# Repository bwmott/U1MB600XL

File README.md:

# Ultimate 1MB 600XL Adapter
The Ultimate 1MB 600XL Adapter is an open hardware PCB that helps with installing an Ultimate 1MB upgrade into an Atari 600XL computer. The [Ultimate 1MB](https://lotharek.pl/productdetail.php?id=56) is a popular upgrade for Atari 8-bit computers, which expands the system's memory to 1MB of RAM, offers a selectable flash memory-based ROM, and includes a Real Time Clock module. Prior to installing an Ultimate 1MB into an Atari 600XL computer, the system must be upgraded to 64KB of RAM (stock 600XLs only contain 16KB of RAM). There are several options for [upgrading a 600XL to 64KB](https://www.mathyvannisselroy.nl/xl600k64.htm).

The Ultimate 1MB 600XL Adapter allows the Ultimate 1MB to be installed in an Atari 600XL without any modifications to the case or motherboard (beyond soldering fours wires required by the Ultimate 1MB) and enables the RF shielding to be retained, if desired. Retaining the RF shielding requires relocating the coin cell battery holder from the Ultimate 1MB board to the Ultimate 1MB 600XL Adapter board.

## Components
In addition to an Ultimate 1MB and an Ultimate 1MB 600XL Adapter PCB, you'll need the following components to complete the build:

* (1) 2x5 10 Pos Receptacle (DigiKey A32955-ND; 6.73mm height) (U1MB_P2P4)
* (1) 2x10 20 Pos Receptacle (DigiKey A26490-ND; 6.73mm height) (U1MB_P5)
* (1) 2x15 30 Pos Receptacle (DigiKey A26494-ND; 6.73mm height) (U1MB_P1)
* (2) 12 Pin Header (DigiKey SAM1101-12-ND; low profile) (BASIC_U4)
* (1) 2 Pin Right Angle Header (U1MB_BAT1)
* (1) 4 Pin Right Angle Header (CPU_P2)
* (1) 5 Pin Right Angle Header (AUX_P4)
* (1) 2x10 20 Pin Right Angle Header (MMU_U2)
* (2) 0.1UF 25V Cap 0603 (DigiKey 732-7989-1-ND) (C1 & C2). (These can be skipped.)

If you would like to retain the RF shielding then the 2x5, 2x10, and 2x15 receptacles that the Ultimate 1MB upgrade plugs into should be no more than 6.73mm tall. In addition, a pair of low profile pin headers must be used on the adapter to plug into the 600XL's BASIC socket. The DigiKey part numbers listed above are versions that allow retaining the RF shielding. (To reduce the potential for damaging the BASIC socket, round pin headers such as Digikey part number SAM1000-12-ND are likely better than the square ones listed above; however, this hasn't been tested.) If you're not planning on retaining the RF shielding, then cheaper receptacles and pin headers can be utilized.

## Adapter Assembly
Here are all the parts and the PCB prior to building the Ultimate 1MB 600XL Adapter board.

Here are photos of the top and bottom of the Ultimate 1MB 600XL Adapter board after all of the components have been assembled.

Here we see the board after transplanting the coil cell battery holder from the Ultimate 1MB to the Ultimate 1MB Adapter board and running wires back to the Ultimate 1MB to provide power for its RTC. Be extra careful not to reverse the connection to the battery. We also see some insulation added on top of the BASIC pin headers to ensure that none of the pins accidentally touch the ROM socket pins on the Ultimate 1MB board when the two boards are plugged together.

## Adapter Installation
The Ultimate 1MB plugs directly on top of the Ultimate 1MB 600XL Adapter board once assembled. The adapter board can then be plugged into the 600XL's BASIC socket after removing both the BASIC and OS ROMs from the 600XL. The adapter board is designed such that the "jumper" settings on the motherboard for the type of BASIC ROM should not matter; however, the adapter board has only been tested using a stock NTSC 600XL.

You'll also need to connect the MMU cable and other motherboard signals to the adapter board like they are in a standard Ultimate 1MB installation. 

If you're retaining the RF shielding then you'll need to ensure the top of the Ultimate 1MB is insulated from the RF shield. A small piece of plastic attached to the board should work fine.

## Acknowledgements
* SukkoPera for the [DIP-24_W15.24mm-Notch KiCad foorprint](https://github.com/SukkoPera/Open2327RomAdapter/) which is used to provide a better 3D preview of the Ultimate 1MB 600XL Adapter.
* Michael St. Pierre for the Ultimate 1MB socket schematics used in the [1088 XEL Mini-ITX Motherboard](https://ataribits.weebly.com/1088xel.html) which were referenced during the design of the Ultimate 1MB 600XL Adapter.

## License
Copyright (c) 2021 by Bradford W. Mott. This source describes Open Hardware and is licensed under the CERN-OHL-W v2.

You may redistribute and modify this source and make products using it under the terms of the CERN-OHL-W v2 or later (https:/cern.ch/cern-ohl). This source is distributed WITHOUT ANY EXPRESS OR IMPLIED WARRANTY, INCLUDING OF MERCHANTABILITY, SATISFACTORY QUALITY AND FITNESS FOR A PARTICULAR PURPOSE. Please see the CERN-OHL-W v2 for applicable conditions.

Source location: https://github.com/bwmott/U1MB600XL

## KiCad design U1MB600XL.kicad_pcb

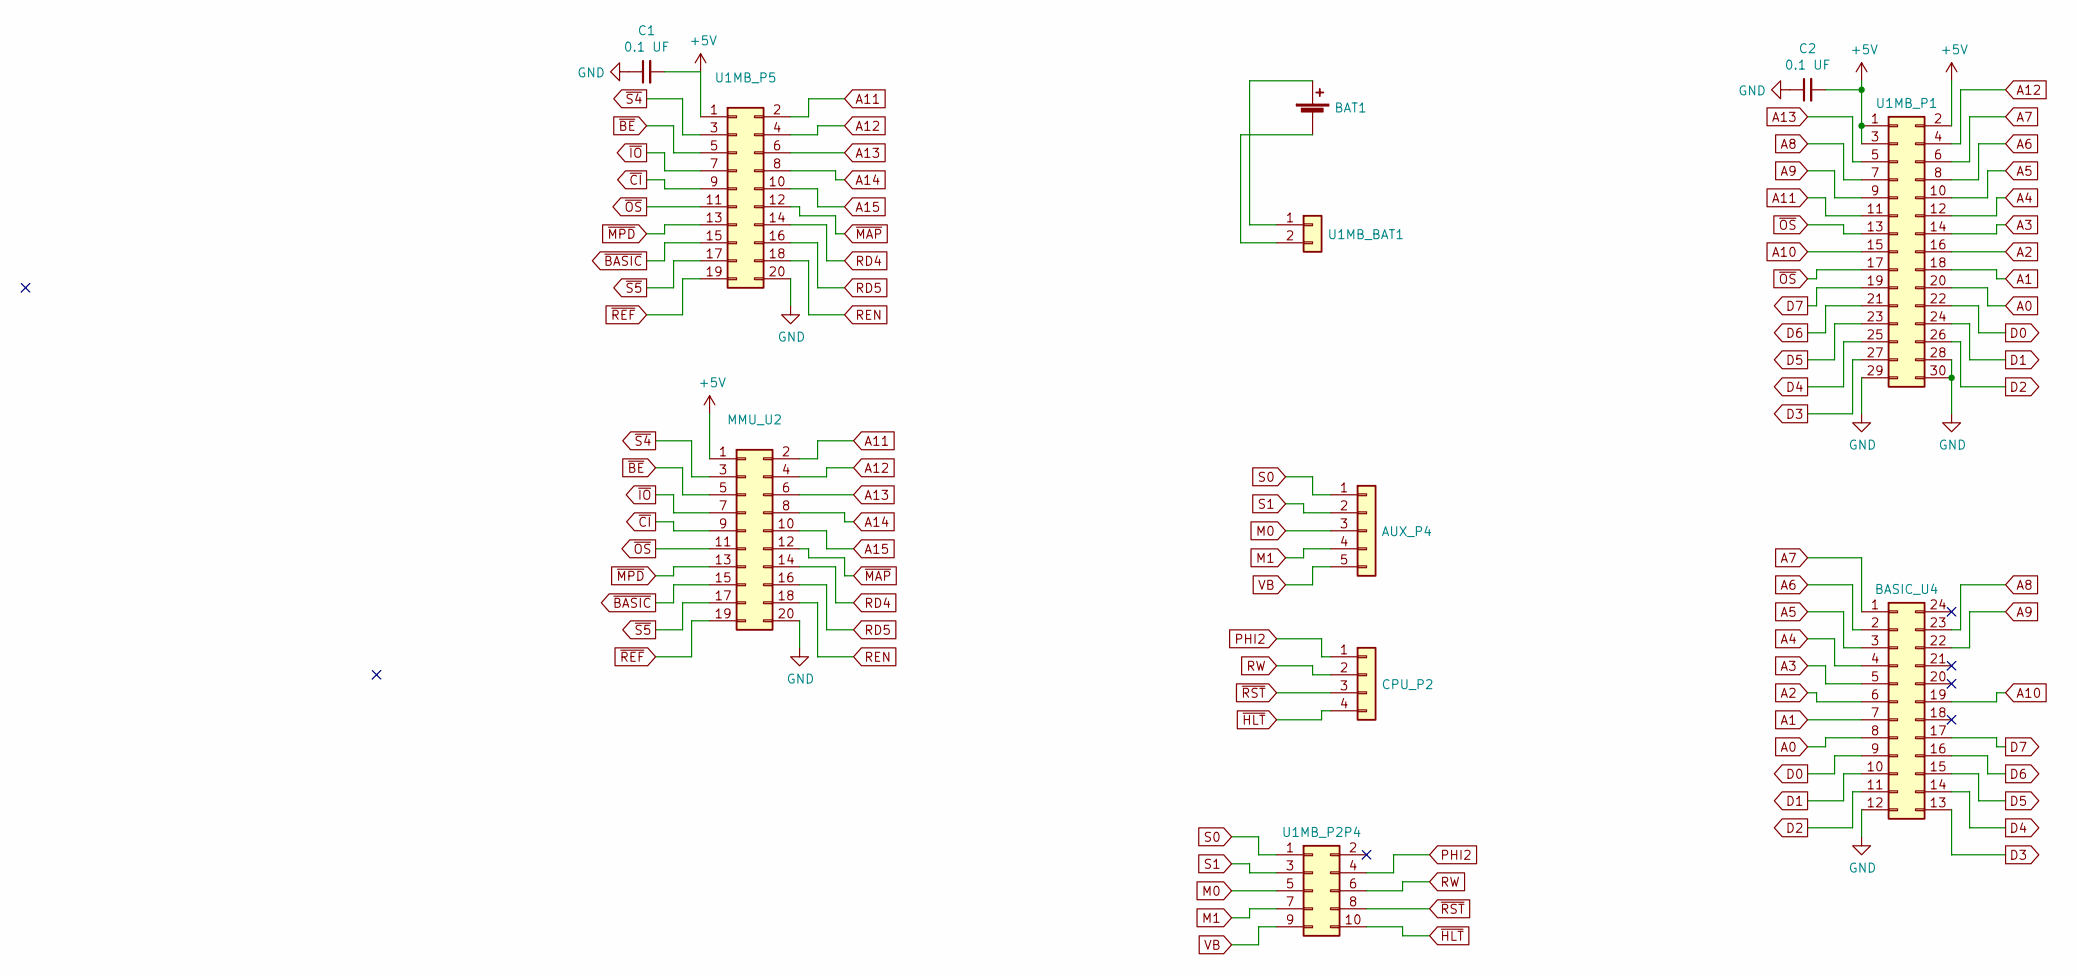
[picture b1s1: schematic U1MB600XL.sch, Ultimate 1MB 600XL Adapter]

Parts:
AUX_P4: Conn_01x05; PinHeader_1x05_P2.54mm_Horizontal
BASIC_U4: Conn_02x12_Counter_Clockwise; DIP-24_W15.24mm-Notch
BAT1: Battery_Cell; BatteryHolder_Keystone_1060_1x2032
C1, C2: 0.1 UF; C_0603_1608Metric
CPU_P2: Conn_01x04; PinHeader_1x04_P2.54mm_Horizontal
MMU_U2: Conn_02x10_Odd_Even; IDC-Header_2x10_P2.54mm_Horizontal
U1MB_BAT1: Conn_01x02; PinHeader_1x02_P2.54mm_Horizontal
U1MB_P1: Conn_02x15_Counter_Clockwise; PinSocket_2x15_P2.54mm_Vertical
U1MB_P2P4: Conn_02x05_Row_Letter_First; PinSocket_2x05_P2.54mm_Vertical
U1MB_P5: Conn_02x10_Odd_Even; PinSocket_2x10_P2.54mm_Vertical

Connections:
+5V: C1.2, C2.2, MMU_U2.1, U1MB_P1.1, U1MB_P1.2, U1MB_P1.3, U1MB_P5.1
A0: BASIC_U4.8, U1MB_P1.20
A1: BASIC_U4.7, U1MB_P1.18
A2: BASIC_U4.6, U1MB_P1.16
A3: BASIC_U4.5, U1MB_P1.14
A4: BASIC_U4.4, U1MB_P1.12
A5: BASIC_U4.3, U1MB_P1.10
A6: BASIC_U4.2, U1MB_P1.8
A7: BASIC_U4.1, U1MB_P1.6
A8: BASIC_U4.23, U1MB_P1.7
A9: BASIC_U4.22, U1MB_P1.9
A10: BASIC_U4.19, U1MB_P1.15
A11: MMU_U2.2, U1MB_P1.11, U1MB_P5.2
A12: MMU_U2.4, U1MB_P1.4, U1MB_P5.4
A13: MMU_U2.6, U1MB_P1.5, U1MB_P5.6
A14: MMU_U2.8, U1MB_P5.8
A15: MMU_U2.10, U1MB_P5.10
D0: BASIC_U4.9, U1MB_P1.22
D1: BASIC_U4.10, U1MB_P1.24
D2: BASIC_U4.11, U1MB_P1.26
D3: BASIC_U4.13, U1MB_P1.27
D4: BASIC_U4.14, U1MB_P1.25
D5: BASIC_U4.15, U1MB_P1.23
D6: BASIC_U4.16, U1MB_P1.21
D7: BASIC_U4.17, U1MB_P1.19
GND: BASIC_U4.12, C1.1, C2.1, MMU_U2.20, U1MB_P1.28, U1MB_P1.29, U1MB_P1.30, U1MB_P5.20
M0: AUX_P4.3, U1MB_P2P4.5
M1: AUX_P4.4, U1MB_P2P4.7
unnamed: BAT1.1 (+), U1MB_BAT1.1
unnamed: BAT1.2 (-), U1MB_BAT1.2
PHI2: CPU_P2.1, U1MB_P2P4.4
RD4: MMU_U2.14, U1MB_P5.14
RD5: MMU_U2.16, U1MB_P5.16
REN: MMU_U2.18, U1MB_P5.18
RW: CPU_P2.2, U1MB_P2P4.6
S0: AUX_P4.1, U1MB_P2P4.1
S1: AUX_P4.2, U1MB_P2P4.3
VB: AUX_P4.5, U1MB_P2P4.9
~BASIC: MMU_U2.15, U1MB_P5.15
~BE: MMU_U2.5, U1MB_P5.5
~CI: MMU_U2.9, U1MB_P5.9
~HLT: CPU_P2.4, U1MB_P2P4.10
~IO: MMU_U2.7, U1MB_P5.7
~MAP: MMU_U2.12, U1MB_P5.12
~MPD: MMU_U2.13, U1MB_P5.13
~OS: MMU_U2.11, U1MB_P1.13, U1MB_P1.17, U1MB_P5.11
~REF: MMU_U2.19, U1MB_P5.19
~RST: CPU_P2.3, U1MB_P2P4.8
~S4: MMU_U2.3, U1MB_P5.3
~S5: MMU_U2.17, U1MB_P5.17

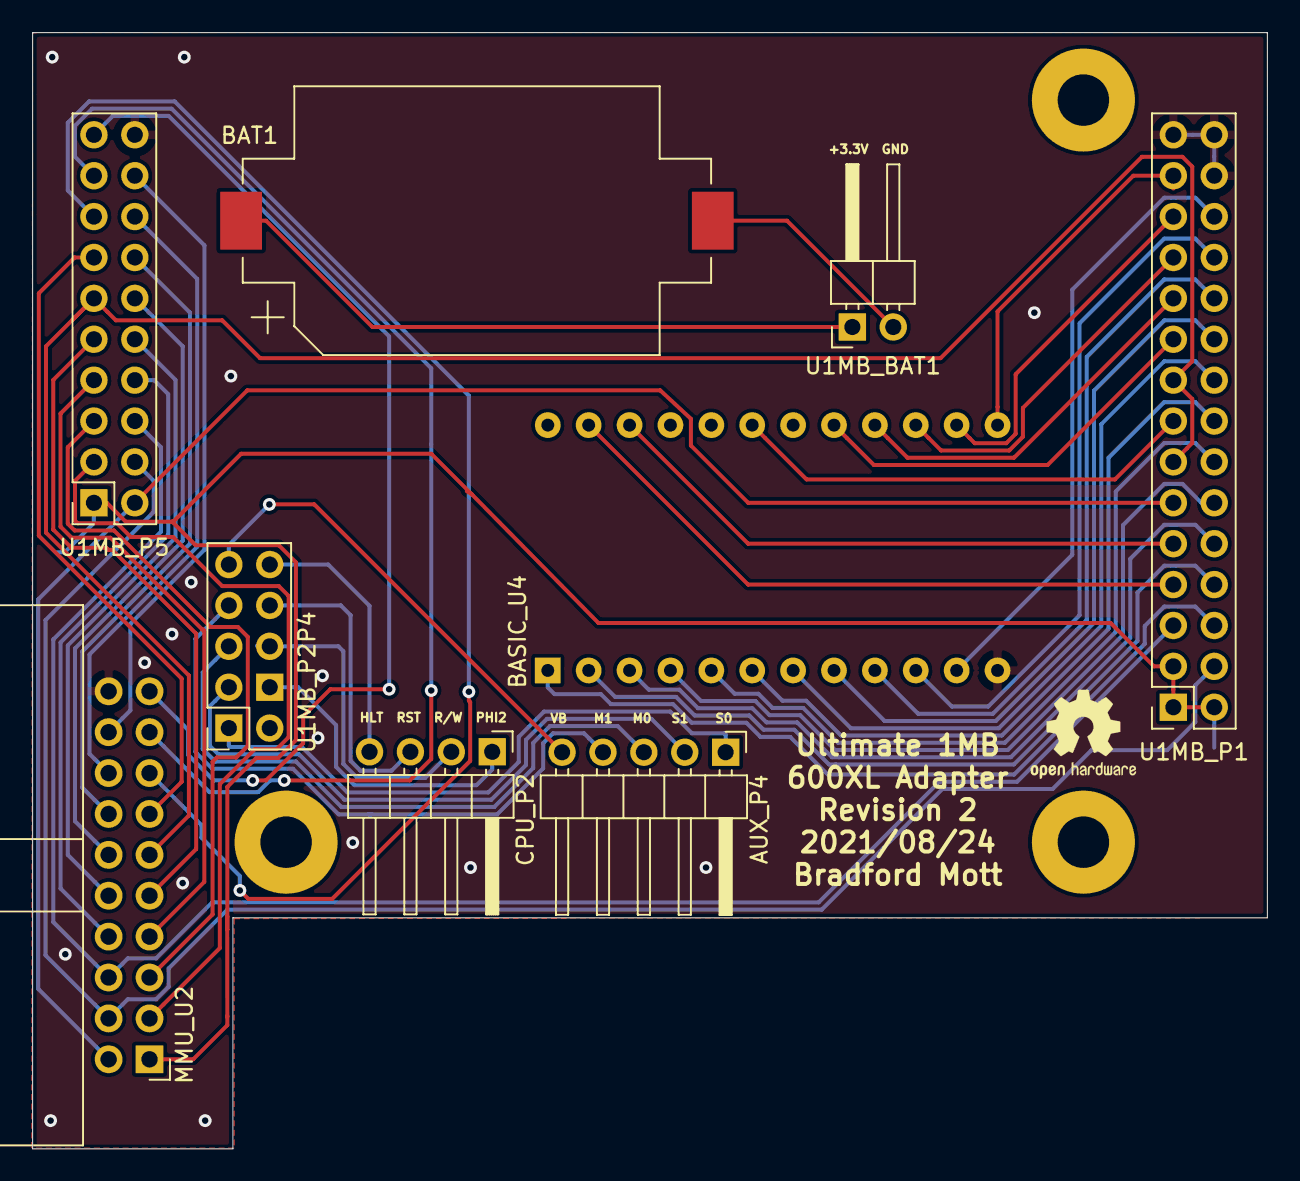
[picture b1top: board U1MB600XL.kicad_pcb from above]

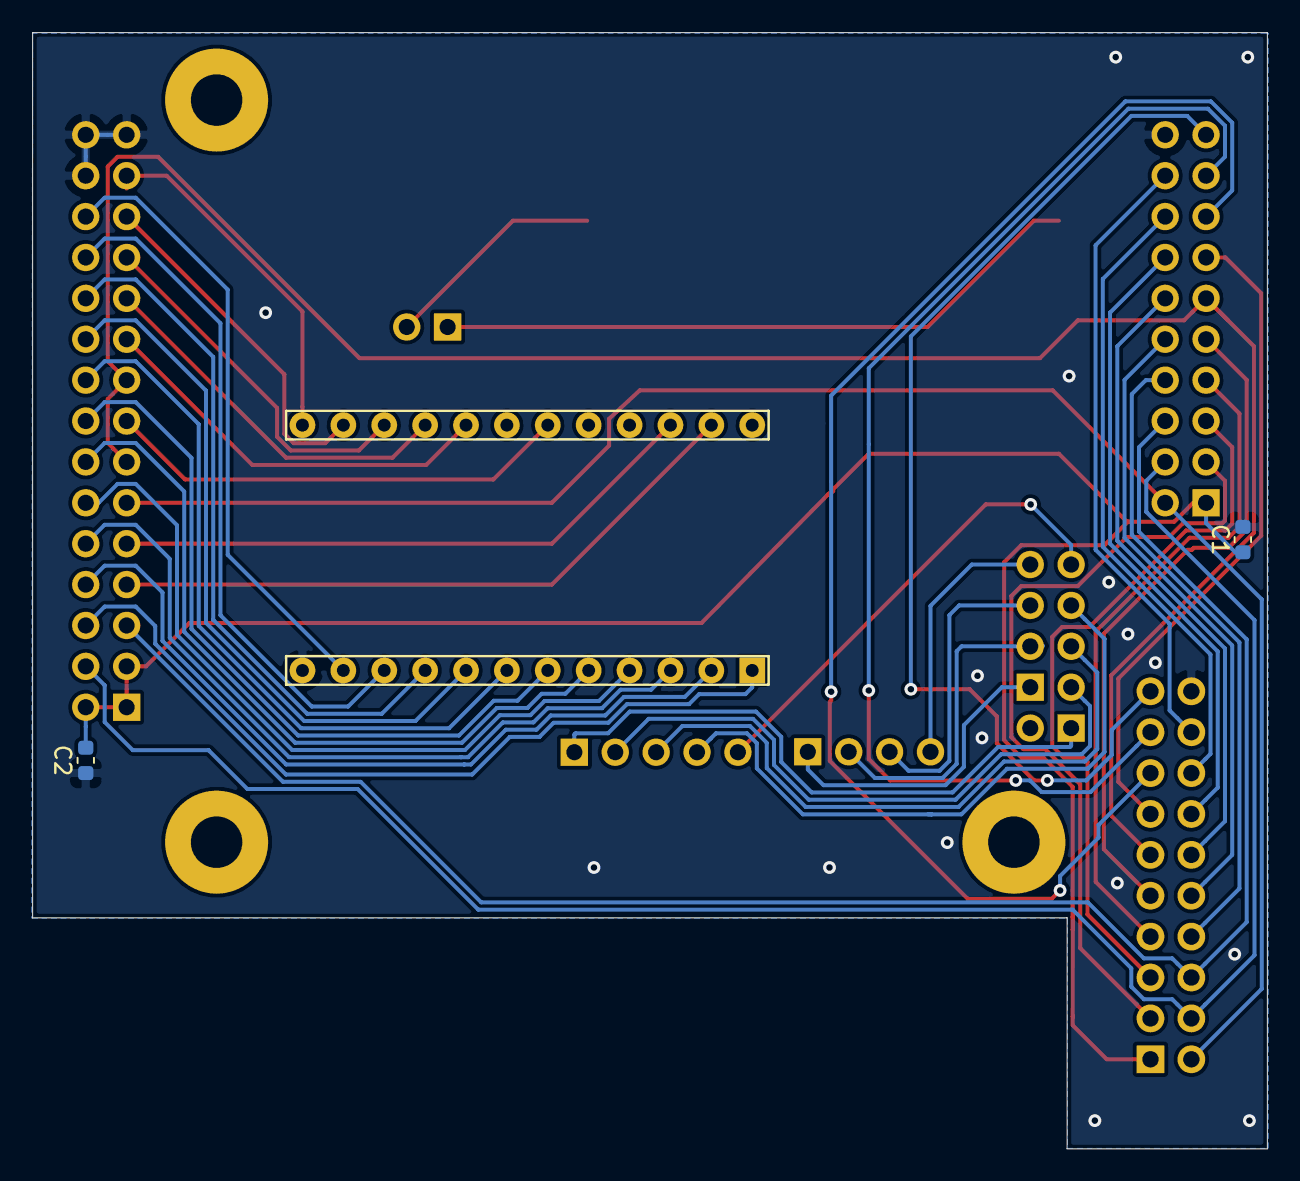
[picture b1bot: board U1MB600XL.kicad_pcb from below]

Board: 2 copper layers, 76.7 x 69.3 mm, 14 parts (2 on the bottom side), 50 nets.

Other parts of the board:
M1, M2, M3: MountingHole_3.2mm_M3_Pad

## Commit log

2021-08-31 Initial commit of design.
2021-09-01 Some initial text for the README.
2022-01-17 Updating readme and adding some photo of building and installing the board.
2022-01-17 Updates to the readme file.
2022-01-17 More updates to the readme file.

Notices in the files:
U1MB600XL.kicad_pcb:
Licensed under CERN-OHL-W v2 or later
